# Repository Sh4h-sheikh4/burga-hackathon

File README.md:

# Burga Hackathon — Fire-spotting Pi quad

End-to-end prototype for a **5″ X-frame drone** that carries a Raspberry Pi, IMU HAT, and USB camera, uploads frames to **TigerData**, and runs a fire-assessment model.

Built for hackathon judges: open the folders below top-to-bottom.

---

## What’s in the repo

| Folder | What it is |
|---|---|
| [`cad/`](cad/) | SolidWorks **finished drone assembly** (frame + motors + Pi + HAT + battery + camera) |
| [`pcb/`](pcb/) | KiCad **Pi HAT** (LSM6DS3TR-C IMU over SPI) |
| [`pid-controller/`](pid-controller/) | Pi **attitude PID** → X-quad mixer → ESC PWM |
| [`firedrone/`](firedrone/) | Capture / upload / TigerData worker pipeline |
| [`model/`](model/) | CNN trainer + predict CLI for fire presence + severity |
| [`demo_artifacts/`](demo_artifacts/) | Pretrained **smoke-demo** model weights |
| [`demo_images/`](demo_images/) | Tiny synthetic image set for a quick demo |
| [`docs/`](docs/) | Hardware BOM / thrust notes + PCB renders |
| [`config/`](config/) · [`sql/`](sql/) · [`deploy/`](deploy/) | Runtime config, DB schema, systemd units |
| [`tests/`](tests/) · [`tools/`](tools/) | Pytest suite and helper scripts |

---

## Quick story for judges

1. **Airframe** — 5″ X-frame CAD sized for ~800 g AUW ([`cad/`](cad/), [`docs/HARDWARE.md`](docs/HARDWARE.md)).
2. **Sense** — custom HAT reads the IMU over SPI ([`pcb/`](pcb/)).
3. **Fly (software)** — complementary filter + roll/pitch PID on the Pi ([`pid-controller/`](pid-controller/)).
4. **See fire** — USB frames → TigerData → CNN worker → assessments ([`firedrone/`](firedrone/), [`model/`](model/)).

---

## Fastest laptop demo (no Pi required)

```bash
python -m venv .venv
# Windows: .venv\Scripts\activate
pip install -r requirements-laptop.txt
# Install a CPU PyTorch build for your platform, then:

python tools/make_smoke_dataset.py
python model/train_predict.py train --data smoke_data --out demo_artifacts --domain rgb --epochs 8 --size 64
```

Full TigerData laptop walkthrough: [`HACKATHON_LAPTOP.md`](HACKATHON_LAPTOP.md).  
Copy `.env.example` → `.env` and set `FIREDRONE_DB_URL` (never commit real secrets).

---

## Hardware snapshot (5″ / 4S)

| Role | Part |
|---|---|
| Motors ×4 | iFlight XING-E Pro 2207 2450KV |
| ESC | SpeedyBee BLS 50A 30×30 |
| Battery | CNHL Black 4S 2200 mAh |
| Compute | Raspberry Pi + Hackathon IMU HAT |
| Pi power | 5 V ≥3 A UBEC from the 4S pack |
| Design AUW | ~800 g → peak TWR ~7:1 |

Details: [`docs/HARDWARE.md`](docs/HARDWARE.md).

---

## Safety

First motor tests **props off or tethered**. The PID loop starts **disarmed**. Never put motor voltage on Pi GPIO.

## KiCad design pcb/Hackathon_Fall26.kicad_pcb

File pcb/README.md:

# PCB — Raspberry Pi IMU HAT

KiCad 10 project for the hackathon **Pi HAT** with an **LSM6DS3TR-C** IMU on **SPI**.

## Open in KiCad

- `Hackathon_Fall26.kicad_pro` — project  
- `Hackathon_Fall26.kicad_sch` — schematic  
- `Hackathon_Fall26.kicad_pcb` — board  

Renders (top/bottom/copper/schematic) are in [`docs/renders/`](../docs/renders/).

## Notes for judges

- Designed as a Pi HAT; the IMU does **not** back-power the Pi (3V3 only from the Pi).  
- Pipeline software expects the IMU on **SPI** (see `firedrone` IMU config).  
- Power the Pi from a separate **5 V UBEC** off the 4S pack — see [`docs/HARDWARE.md`](../docs/HARDWARE.md).

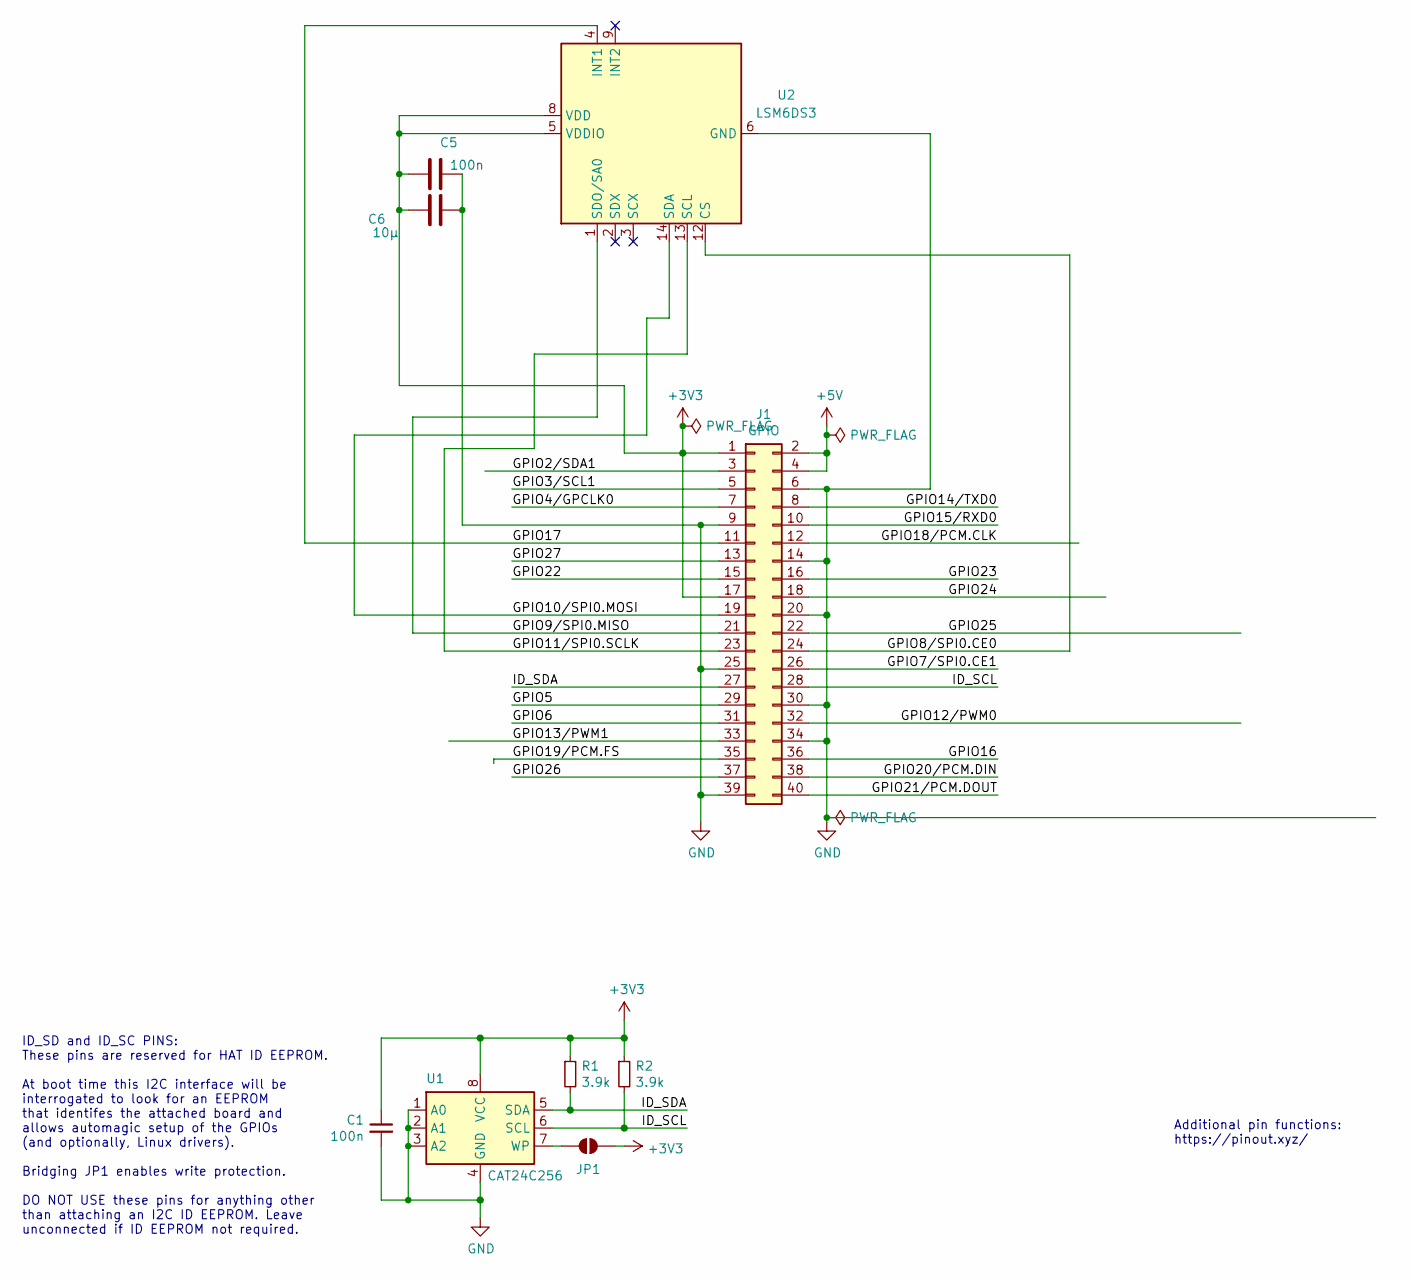
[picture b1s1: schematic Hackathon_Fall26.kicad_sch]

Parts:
C1, C5: 100n; C_0603_1608Metric
C6: 10μ; C_0805_2012Metric
J1: GPIO; PinSocket_2x20_P2.54mm_Vertical
JP1: ID_WP; PinHeader_1x02_P2.54mm_Vertical
R1, R2: 3.9k; R_Axial_DIN0207_L6.3mm_D2.5mm_P10.16mm_Horizontal
U1: CAT24C256; SOIC-8_3.9x4.9mm_P1.27mm
U2: LSM6DS3; LGA-14_3x2.5mm_P0.5mm_LayoutBorder3x4y

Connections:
+3V3: C1.1, C5.1, C6.1, J1.1, J1.17, JP1.2 (B), R1.1, R2.1, U1.8 (VCC), U2.5 (VDDIO), U2.8 (VDD)
+5V: J1.2, J1.4
/GPIO2/SDA1: J1.3
/GPIO3/SCL1: J1.5
/GPIO4/GPCLK0: J1.7
/GPIO5: J1.29
/GPIO6: J1.31
/GPIO7/SPI0.CE1: J1.26
/GPIO8/SPI0.CE0: J1.24, U2.12 (CS)
/GPIO9/SPI0.MISO: J1.21, U2.1 (SDO/SA0)
/GPIO10/SPI0.MOSI: J1.19, U2.14 (SDA)
/GPIO11/SPI0.SCLK: J1.23, U2.13 (SCL)
/GPIO12/PWM0: J1.32
/GPIO13/PWM1: J1.33
/GPIO14/TXD0: J1.8
/GPIO15/RXD0: J1.10
/GPIO16: J1.36
/GPIO17: J1.11, U2.4 (INT1)
/GPIO18/PCM.CLK: J1.12
/GPIO19/PCM.FS: J1.35
/GPIO20/PCM.DIN: J1.38
/GPIO21/PCM.DOUT: J1.40
/GPIO22: J1.15
/GPIO23: J1.16
/GPIO24: J1.18
/GPIO25: J1.22
/GPIO26: J1.37
/GPIO27: J1.13
/ID_SCL: J1.28, R2.2, U1.6 (SCL)
/ID_SDA: J1.27, R1.2, U1.5 (SDA)
GND: C1.2, C5.2, C6.2, J1.6, J1.9, J1.14, J1.20, J1.25, J1.30, J1.34, J1.39, U1.1 (A0), U1.2 (A1), U1.3 (A2), U1.4 (GND), U2.6 (GND), U2.7 (GND)
unnamed: JP1.1 (A), U1.7 (WP)

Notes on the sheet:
Additional pin functions: https://pinout.xyz/
ID_SD and ID_SC PINS: These pins are reserved for HAT ID EEPROM. At boot time this I2C interface will be interrogated to look for an EEPROM that identifes the attached board and allows automagic setup of the GPIOs (and optionally, Linux drivers). Bridging JP1 enables write protection. DO NOT USE th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

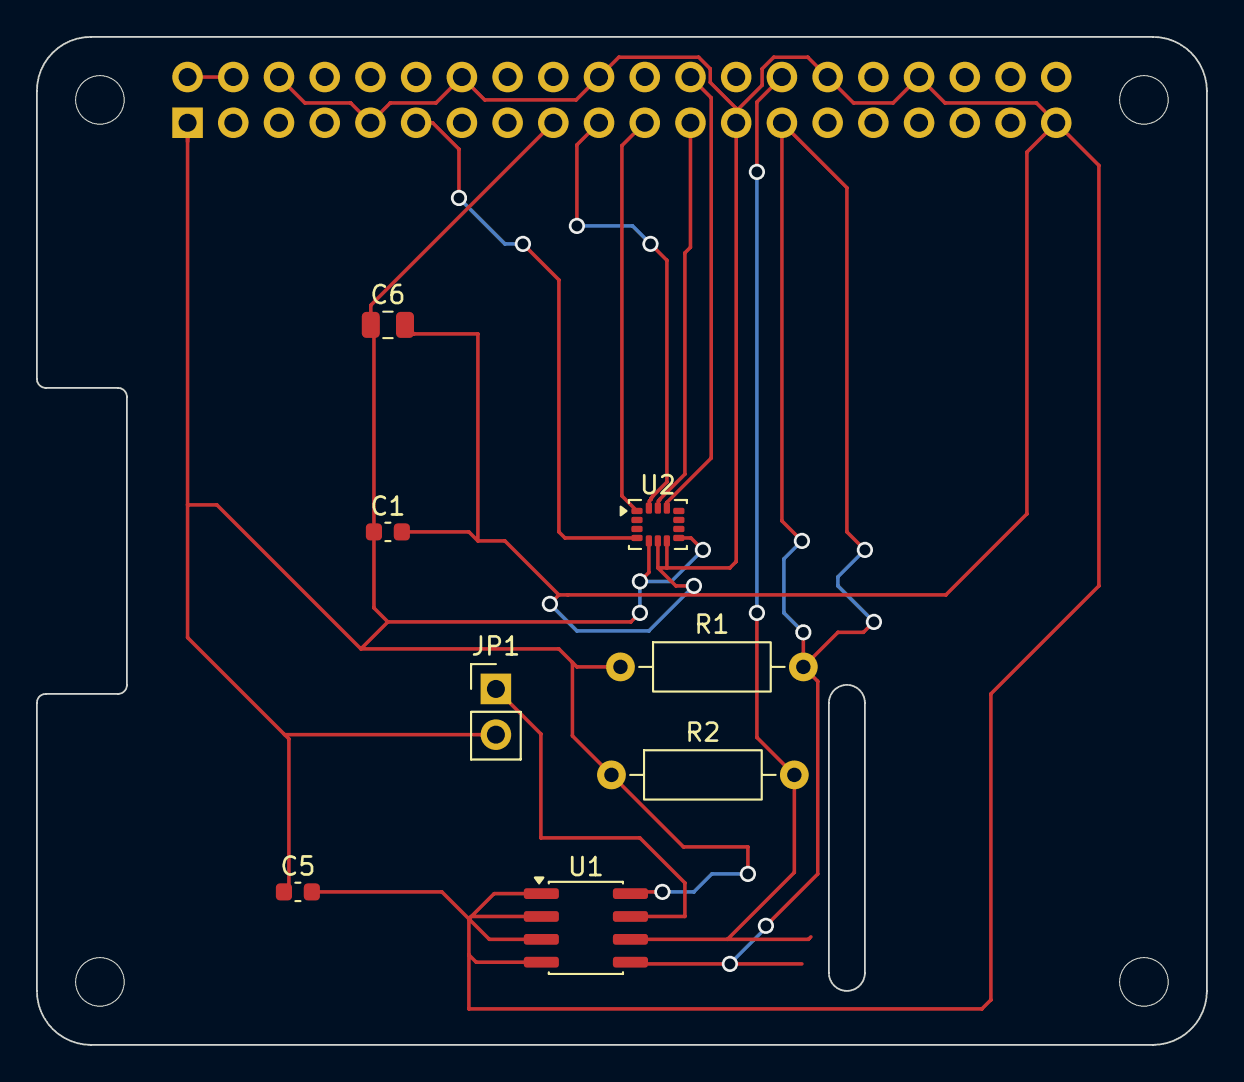
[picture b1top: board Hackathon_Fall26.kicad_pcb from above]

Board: 2 copper layers, 65.0 x 56.0 mm, 13 parts (1 on the bottom side), 11 nets.

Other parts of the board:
MH1, MH2, MH3, MH4: MountingHole_2.7mm_M2.5

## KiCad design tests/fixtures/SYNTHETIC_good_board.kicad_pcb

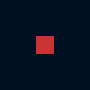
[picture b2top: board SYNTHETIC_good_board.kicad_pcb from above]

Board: 2 copper layers, 4 parts (0 on the bottom side), 5 nets, no tracks yet.

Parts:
C1, C2: 100nF; C_0402_1005Metric
J1: RaspberryPi_GPIO; PinSocket_2x20_P2.54mm_Vertical
U1: LSM6DS3TR-C; LGA-14_3x2.5mm_P0.5mm_LayoutBorder3x4y

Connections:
+3V3: C1.1, C2.1, J1.1, J1.17, U1.2, U1.3, U1.5, U1.8, U1.12
+5V: J1.2, J1.4
/SCL: J1.5, U1.13
/SDA: J1.3, U1.14
GND: C1.2, C2.2, J1.6, J1.9, J1.14, J1.20, J1.25, J1.30, J1.34, J1.39, U1.1, U1.6, U1.7
